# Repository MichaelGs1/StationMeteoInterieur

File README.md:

# StationMeteoInterieur

<p align="justify">&ensp;&ensp;Projet d'une station méteo permettant de surveiller la température, l'humidité, le taux de CO2 ainsi que le total de particules nocives TVOC. Il permet également de détecter les fumées.
Toutes ces informations sont indiquées sur un écran LCD et des leds informent l'utilisateur d'un taux trop élévés de particules, de CO2 ou de fumée.</p>

### Matériel necéssaire:

- Capteurs :
  - DHT22 (température, humidité)
  - CSS811 (CO2, TVOC)
  - MQ-2 (fumées)
  
- Un écran LCD 4 lignes, 20 caractères en I2C

- Arduino : Nano BLE ou Nano 33 IOT

- Leds 5mm : rouge, verte, bleu

- Transistors : 2 BSS138
- Résistances CMS (0805 imperial) : 3x100Ohms, 4x10kOhms
- Résistance tranversante : 10kOhms
- Condensateurs tranversants : 100uF

- Connecteurs : PinSockets pas de 2.54mm de diverses longueurs

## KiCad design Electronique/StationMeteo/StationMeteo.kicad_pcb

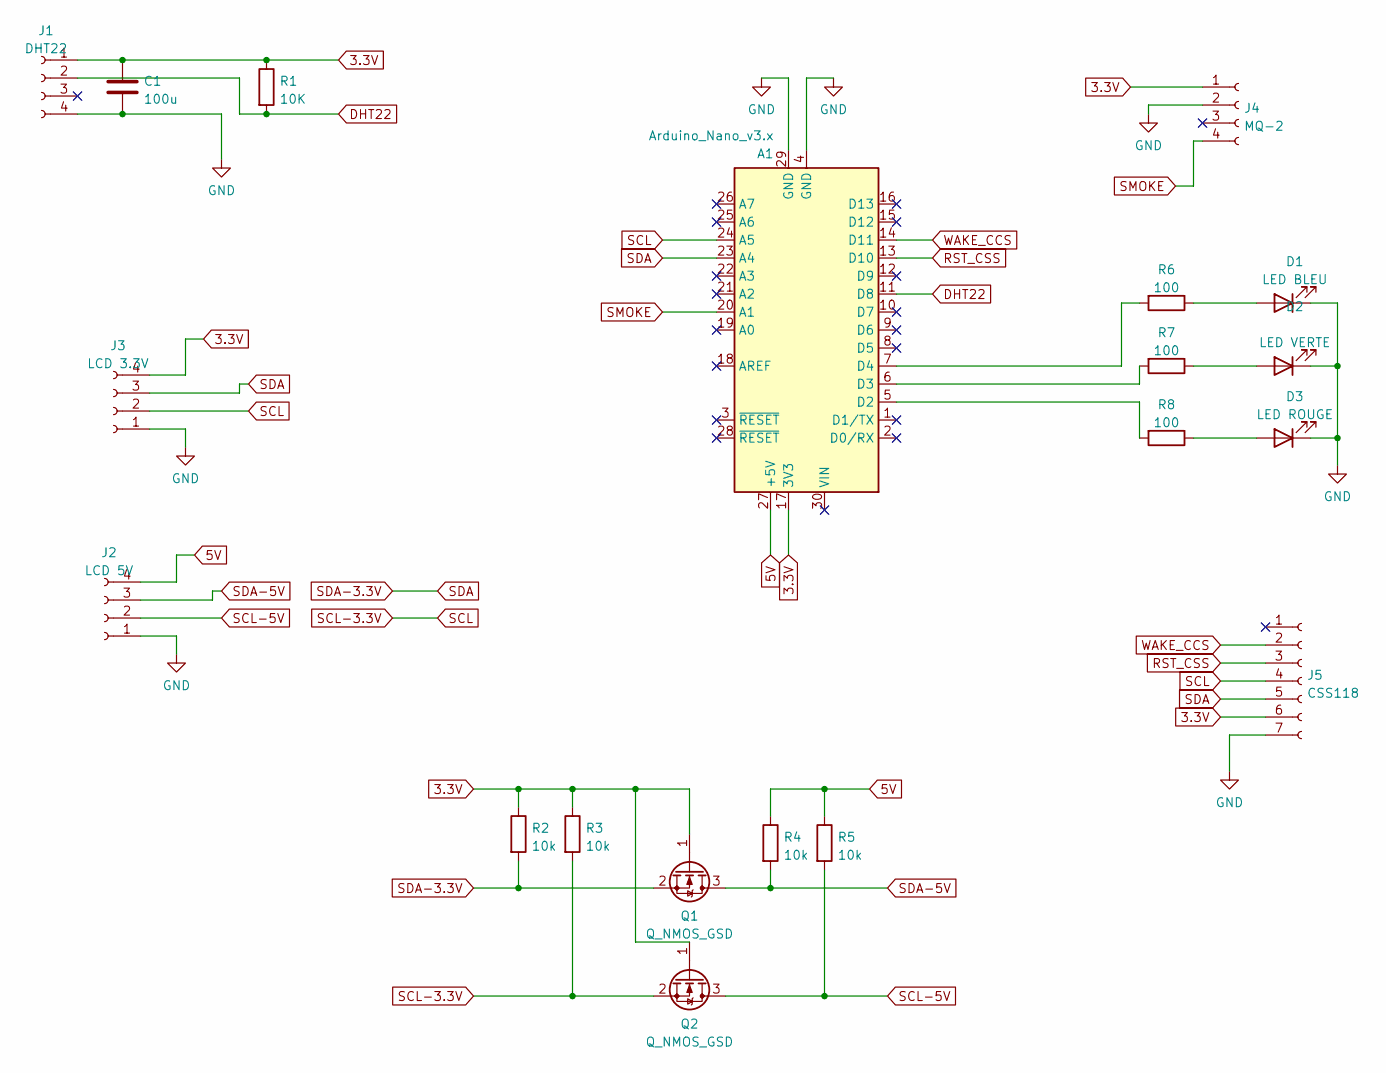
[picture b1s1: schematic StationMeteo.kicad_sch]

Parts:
A1: Arduino_Nano_v3.x; Arduino_Nano
C1: 100u; C_Disc_D4.7mm_W2.5mm_P5.00mm
D1: LED BLEU; LED_D5.0mm
D2: LED VERTE; LED_D5.0mm
D3: LED ROUGE; LED_D5.0mm
J1: DHT22; PinSocket_1x04_P2.54mm_Vertical
J2: LCD 5V; PinSocket_1x04_P2.54mm_Vertical
J3: LCD 3.3V; PinSocket_1x04_P2.54mm_Vertical
J4: MQ-2; PinSocket_1x04_P2.54mm_Vertical
J5: CSS118; PinSocket_1x07_P2.54mm_Vertical
Q1, Q2: Q_NMOS_GSD; SOT-23
R1: 10K; R_Axial_DIN0207_L6.3mm_D2.5mm_P5.08mm_Vertical
R2, R3, R4, R5: 10k; R_0805_2012Metric_Pad1.20x1.40mm_HandSolder
R6, R7, R8: 100; R_0805_2012Metric_Pad1.20x1.40mm_HandSolder

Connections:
3.3V: A1.17 (3V3), C1.1, J1.1, J3.4, J4.1, J5.6, Q1.1 (G), Q2.1 (G), R1.1, R2.1, R3.1
5V: A1.27 (+5V), J2.4, R4.1, R5.1
DHT22: A1.11 (D8), J1.2, R1.2
GND: A1.4 (GND), A1.29 (GND), C1.2, D1.1 (K), D2.1 (K), D3.1 (K), J1.4, J2.1, J3.1, J4.2, J5.7
unnamed: A1.5 (D2), R8.2
unnamed: A1.6 (D3), R7.2
unnamed: A1.7 (D4), R6.2
unnamed: D1.2 (A), R6.1
unnamed: D2.2 (A), R7.1
unnamed: D3.2 (A), R8.1
RST_CSS: A1.13 (D10), J5.3
SCL: A1.24 (A5), J3.2, J5.4, Q2.2 (S), R3.2
SCL-5V: J2.2, Q2.3 (D), R5.2
SDA: A1.23 (A4), J3.3, J5.5, Q1.2 (S), R2.2
SDA-5V: J2.3, Q1.3 (D), R4.2
SMOKE: A1.20 (A1), J4.4
WAKE_CCS: A1.14 (D11), J5.2

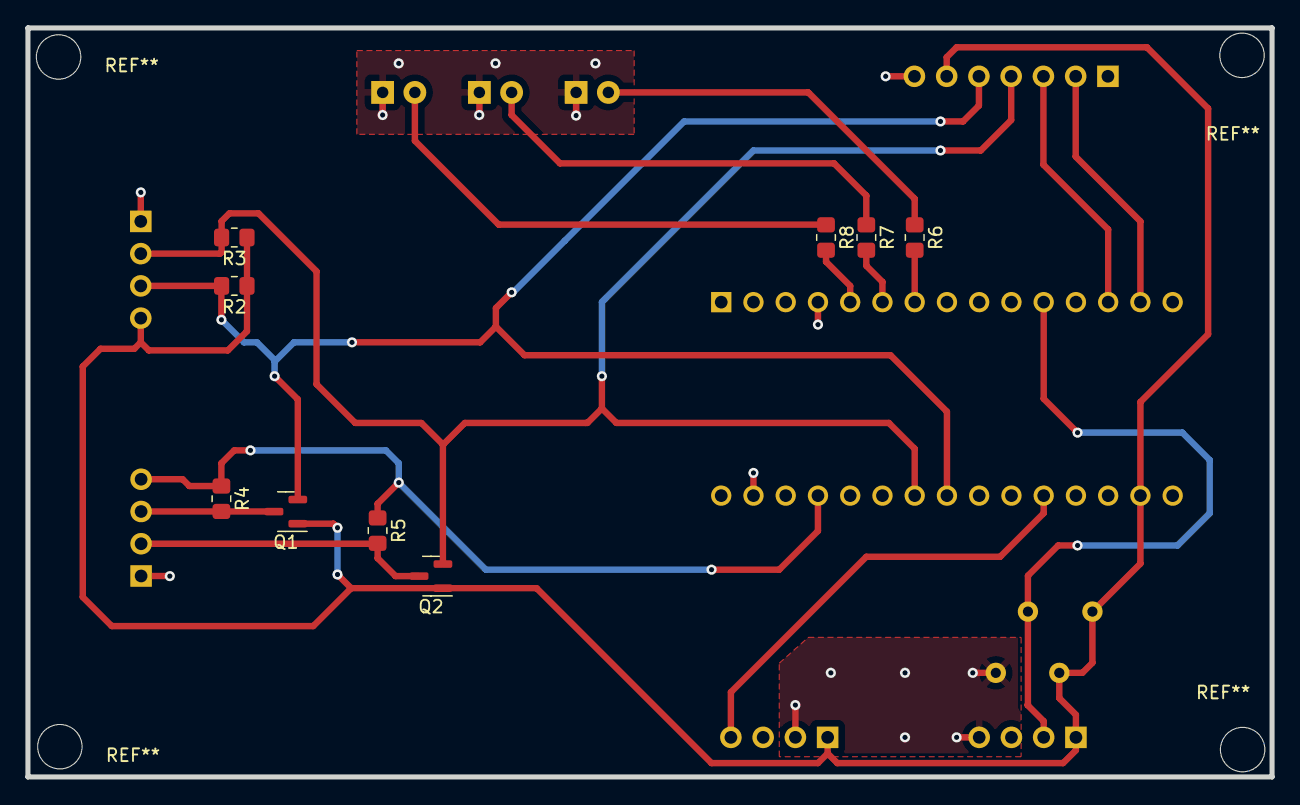
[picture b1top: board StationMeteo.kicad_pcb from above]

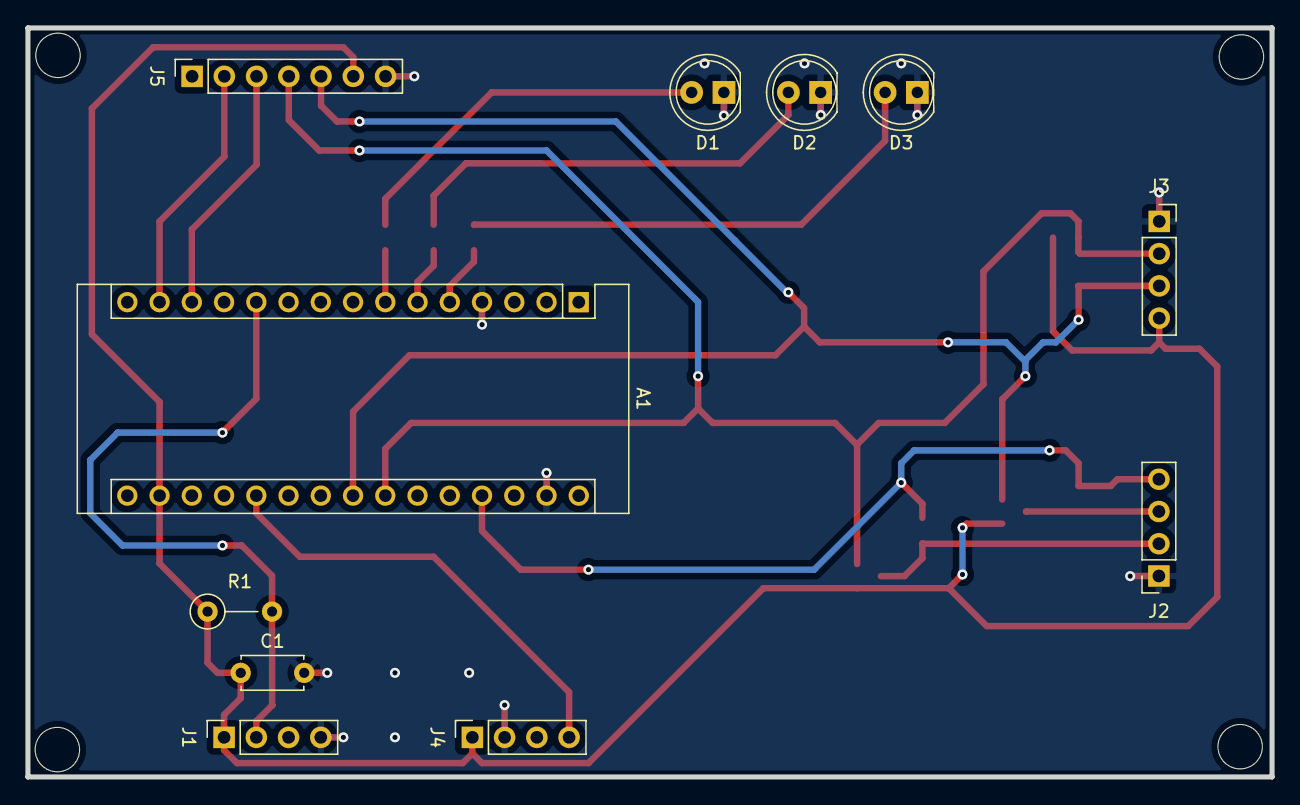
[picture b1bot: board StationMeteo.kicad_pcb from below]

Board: 2 copper layers, 98.0 x 59.0 mm, 20 parts (11 on the bottom side), 17 nets.

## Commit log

2022-06-03 init file
2022-07-02 add temp and humi to polution sensor
2022-07-02 add photos
2022-07-02 fix prototypes
2022-07-03 fix display
